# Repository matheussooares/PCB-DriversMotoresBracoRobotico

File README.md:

# PCB Drivers dos Motores do Braço Robótico

## Esquemático do Circuito Elétrico 

## Layout da Placa de Circuito Impresso 

## Placa de Circuito Impresso 3D

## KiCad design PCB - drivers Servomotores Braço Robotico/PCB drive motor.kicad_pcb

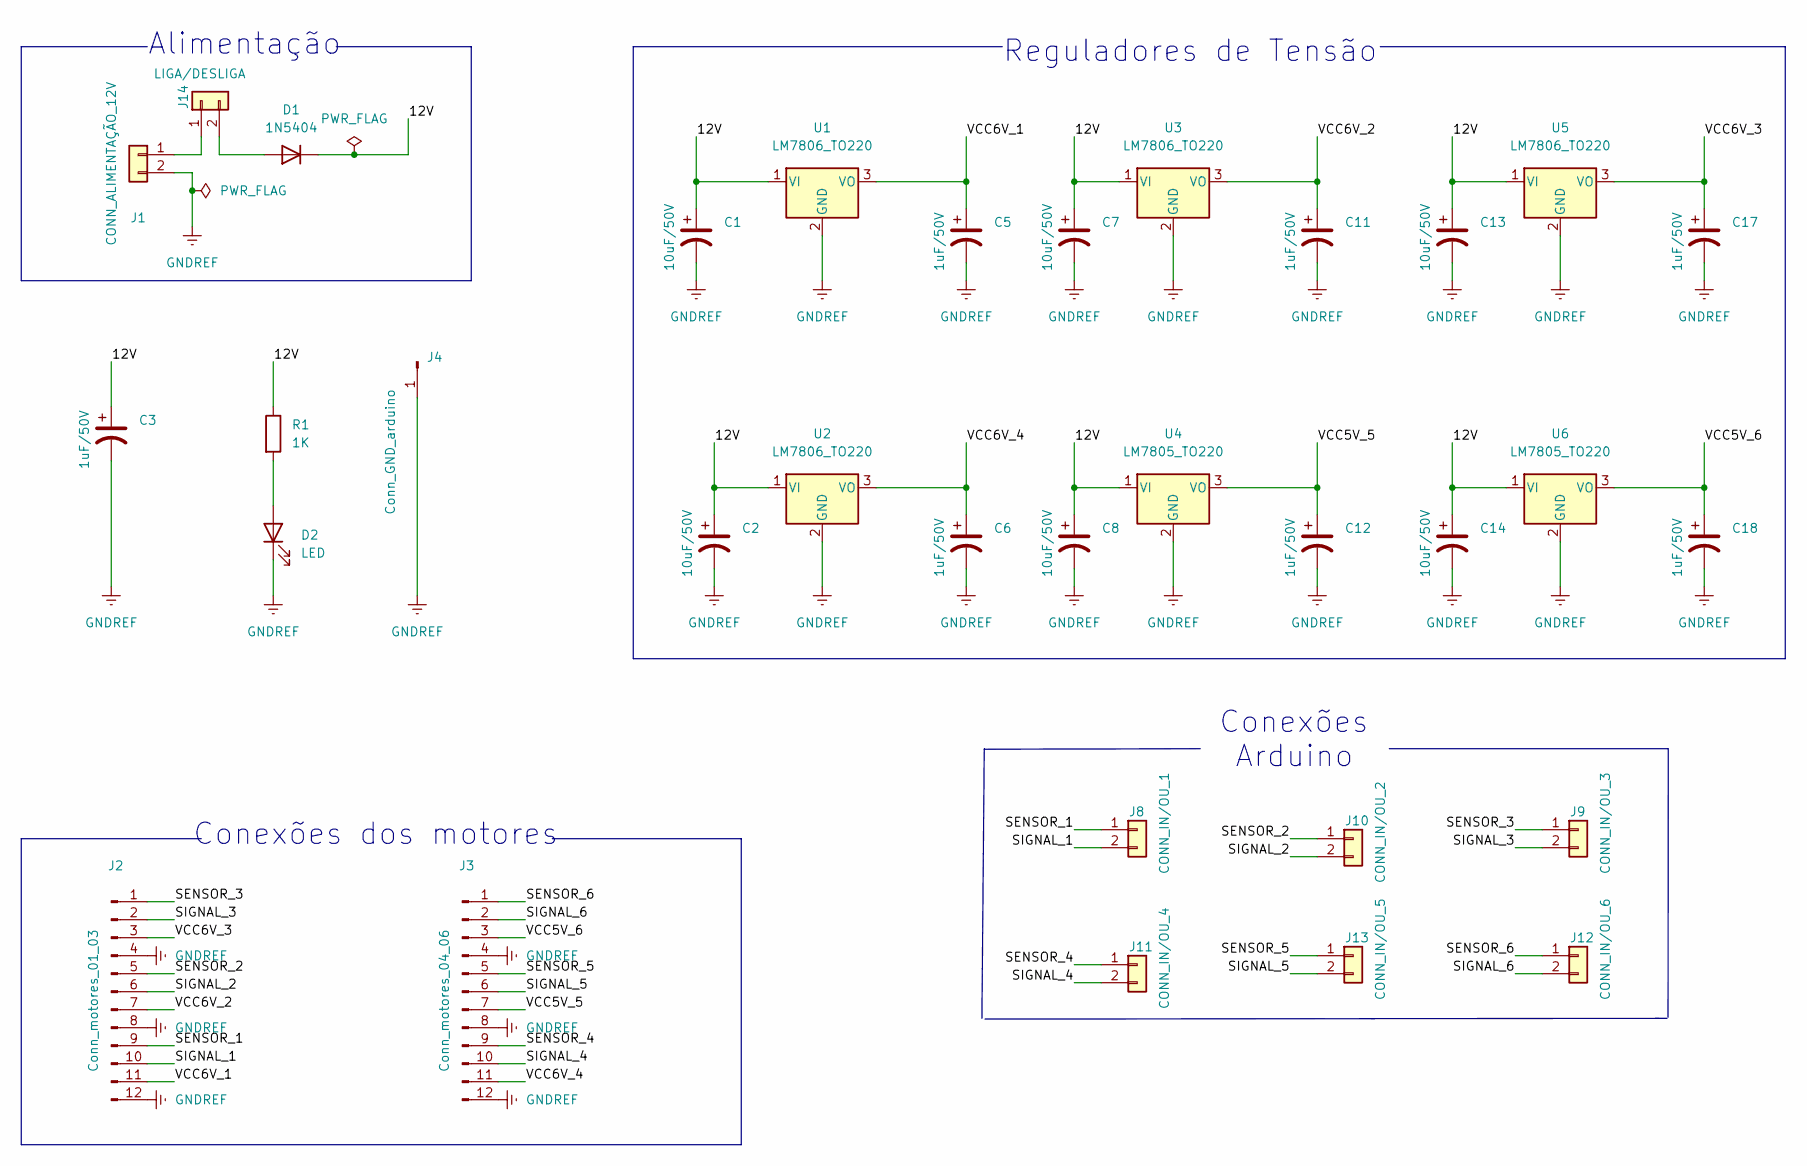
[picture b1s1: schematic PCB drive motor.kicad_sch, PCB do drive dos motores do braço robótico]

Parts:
C1, C2, C7, C8, C13, C14: 10uF/50V; CP_Radial_D5.0mm_P2.50mm
C3, C5, C6, C11, C12, C17, C18: 1uF/50V; CP_Radial_D5.0mm_P2.50mm
D1: 1N5404; D_DO_6A6_DC__P15.24mm_Horizontal_D1.0mm
D2: LED; LED_D5.0mm
J1: CONN_ALIMENTAÇÃO_12V; BarrelJack_GCT_DCJ200-10-A_Horizontal
J2: Conn_motores_01_03; TerminalBlock_Phoenix_MKDS-1,5-12_1x12_P5.00mm_Horizontal
J3: Conn_motores_04_06; TerminalBlock_Phoenix_MKDS-1,5-12_1x12_P5.00mm_Horizontal
J4: Conn_GND_arduino; PinSocket_1x01_P2.54mm_Vertical
J8: CONN_IN/OU_1; PinSocket_1x02_P2.54mm_Vertical
J9: CONN_IN/OU_3; PinSocket_1x02_P2.54mm_Vertical
J10: CONN_IN/OU_2; PinSocket_1x02_P2.54mm_Vertical
J11: CONN_IN/OU_4; PinSocket_1x02_P2.54mm_Vertical
J12: CONN_IN/OU_6; PinSocket_1x02_P2.54mm_Vertical
J13: CONN_IN/OU_5; PinSocket_1x02_P2.54mm_Vertical
J14: LIGA/DESLIGA; PinSocket_1x02_P2.54mm_Vertical
R1: 1K; R_Axial_DIN0207_L6.3mm_D2.5mm_P10.16mm_Horizontal
U1, U2, U3, U5: LM7806_TO220; TO-220-3_Horizontal_TabDown
U4, U6: LM7805_TO220; TO-220-3_Horizontal_TabDown

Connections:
/12V: C1.1, C2.1, C3.1, C7.1, C8.1, C13.1, C14.1, D1.1 (K), R1.1, U1.1 (VI), U2.1 (VI), U3.1 (VI), U4.1 (VI), U5.1 (VI), U6.1 (VI)
/SENSOR_1: J2.9, J8.1
/SENSOR_2: J2.5, J10.1
/SENSOR_3: J2.1, J9.1
/SENSOR_4: J3.9, J11.1
/SENSOR_5: J3.5, J13.1
/SENSOR_6: J3.1, J12.1
/SIGNAL_1: J2.10, J8.2
/SIGNAL_2: J2.6, J10.2
/SIGNAL_3: J2.2, J9.2
/SIGNAL_4: J3.10, J11.2
/SIGNAL_5: J3.6, J13.2
/SIGNAL_6: J3.2, J12.2
/VCC5V_5: C12.1, J3.7, U4.3 (VO)
/VCC5V_6: C18.1, J3.3, U6.3 (VO)
/VCC6V_1: C5.1, J2.11, U1.3 (VO)
/VCC6V_2: C11.1, J2.7, U3.3 (VO)
/VCC6V_3: C17.1, J2.3, U5.3 (VO)
/VCC6V_4: C6.1, J3.11, U2.3 (VO)
GNDREF: C1.2, C2.2, C3.2, C5.2, C6.2, C7.2, C8.2, C11.2, C12.2, C13.2, C14.2, C17.2, C18.2, D2.1 (K), J1.2, J2.4, J2.8, J2.12, J3.4, J3.8, J3.12, J4.1, U1.2 (GND), U2.2 (GND), U3.2 (GND), U4.2 (GND), U5.2 (GND), U6.2 (GND)
unnamed: D1.2 (A), J14.2
unnamed: D2.2 (A), R1.2
unnamed: J1.1, J14.1

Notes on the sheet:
Conexões dos motores
Reguladores de Tensão
Alimentação
Conexões Arduino

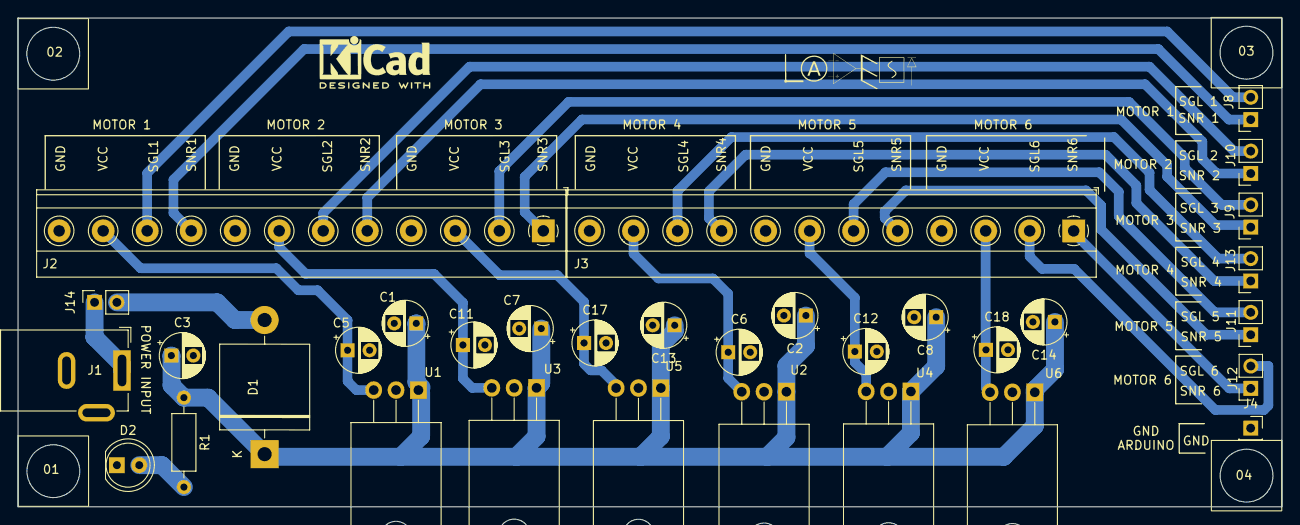
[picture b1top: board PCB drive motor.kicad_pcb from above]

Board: 2 copper layers, 143.6 x 55.5 mm, 37 parts (0 on the bottom side), 23 nets.

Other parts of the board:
01, 02, 03, 04: Furo

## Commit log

2023-08-24 Esquemático e layout da PCB
2023-08-24 Figuras do esquemático e do layout da PCB
2023-08-24 Gerbers e Drills
2023-08-24 Figuras da PCB
2023-08-24 Readme atualizado
